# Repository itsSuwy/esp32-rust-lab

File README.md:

# Rust_ESP32_STD
## Descripcion
Este repositorio nacio de la idea de tener un laboratorio personal de proyectos utilizando una placa de desarrollo ESP32, no obstante, a diferencia de repositorios o proyectos utilizando el mismo hardware, aqui se desarrollaran proyectos con el lenguaje de programacion "**Rust**", mas especificamente a su version STD en arquitectura Xtensa respaldada por Espressif. Ya que Rust en sistemas embebidos, microcontroladores y microprocesadores esta ganando fuerza, por lo que me gustaria aprender y dominar este ambito (no me cierro a trabajar con la version no std a futuro!).  
Por otra parte me gustaria que este repositorio pudiera servir de ayuda con los proyectos ya realizados a quienes estan empezando en este ecosistema, ya que encontrar informacion orientada a std, almenos para mi se me complico encontrar.

## Objetivos del repositorio
Ademas de documentar proyectos realizados y poder ayudar a personas nuevas, me gustaria que el destino manifiesto de este proyecto se apegara a los siguientes lineamientos
- Aprender Rust en sistemas **std**.
- Documentar cada proyecto desde cero.
- Presentar ejemplos reproducibles.
- Mantener buenas practicas en el desarrollo.
- Priorizar soluciones técnicamente correctas y eficientes, manteniendo un código claro y mantenible.
- Aspirar a trabajar con proyectos mas "demandantes" segun vaya progresando en los trabajos.

## Contenido
Dentro de este repositorio existiran multiples carpetas asociadas a un proyecto especifico (blinking-leds, comunicacion UART, etc) las cuales contendran toda la informacion que se utilizo para realizarlo. Dentro de cada trabajo la informacion mantendra un orden jerarquizado en dos categorias principales:
- Codigo: Toda la logica para el funcionamiento, incluira un README.md que explique hace cada parte del codigo asi como los componentes que se utilizaron para crearlo con una protoboard. Segun se progrese en la complejidad del trabajo, se comenzaran a omitir ciertos elementos que ya se explicaron en proyectos pasados, para asi evitar saturar el README.md de informacion que ya ha aparecido en otros proyectos, siguiendo un estilo KISS.
- Hardware: Una carpeta exclusiva dentro del directorio del proyecto, contendra: archivo esquematico, diseño de PCB, Project File, los tres siendo nativos de KiCAD. Tambien se adjuntara una o varias fotos del circuito armado en una Protoboard funcionando.

## Cronologia de actividades
Mi meta es pasar de lo basico a lo particular/nicho con este trabajo orientandolo mas a sistemas IoT, por ende decidi separar por etapas los proyectos a realizar, cada una conteniendo varios proyectos y respetando su enfoque comun. Las fases que decidi seguir son:

### Etapa 1: Fundamentos de hardware abstraction
Primera etapa del aprendizaje. Aqui se desarrollaran las bases para el trabajo en sistemas embebidos enfocadas a comprender el funcionamiento del `HAL` (Hardware Abstraction Layer) proporcionado por la libreria oficial de Espressif para abstraer el acceso al ESP-IDF desde Rust. Se aprende a interactual con los perifericos fundamentales del microcontrolador aplicando funciones de: GPIO, UART, PWM, ADC y temporizadores. Estableciendo los conceptos que serviran de base para etapas posteriores.

### Etapa 2: Patrones de Diseño para Sistemas Embebidos
Etapa enfocada en la construcción de aplicaciones embebidas mediante patrones de diseño fundamentales. A partir de los periféricos estudiados anteriormente, se implementan máquinas de estados, integración de múltiples módulos, control de dispositivos de salida y procesamiento básico de datos provenientes de sensores. El objetivo es desarrollar un diseno de codigo modular, escalable y fácil de mantener, siguiendo una arquitectura que pueda reutilizarse en proyectos de mayor complejidad.

### Etapa 3: Comunicación entre Plataformas
Etapa enfocada en el diseño e implementación de arquitecturas distribuidas mediante la comunicación entre múltiples microcontroladores. Se desarrollan protocolos de intercambio de datos, análisis e interpretación de comandos, asignación de responsabilidades entre dispositivos y coordinación del comportamiento del sistema mediante máquinas de estados distribuidas. El objetivo es comprender cómo construir sistemas embebidos compuestos por varios nodos que colaboran entre sí de forma confiable y escalable.

### Etapa 4: Buses de Comunicación
Etapa dedicada al aprendizaje de los principales protocolos de comunicación utilizados en sistemas embebidos para la interacción con periféricos externos. Se implementan interfaces basadas en **I2C** y **SPI**, comprendiendo su funcionamiento, la conexión de múltiples dispositivos sobre un mismo bus y el desarrollo de interfaces gráficas básicas para la visualización de información. El objetivo es adquirir las bases necesarias para integrar sensores, memorias, pantallas y otros periféricos en aplicaciones embebidas de mayor complejidad.

### Etapa 5: Integración de Sensores
Etapa orientada a la adquisición y procesamiento de datos provenientes de sensores utilizados en aplicaciones embebidas reales. Se trabaja con sensores ambientales, de movimiento, de distancia y convertidores analógico-digitales de alta resolución, abordando tanto protocolos de comunicación como requisitos específicos de temporización y precisión. El objetivo es desarrollar la capacidad de integrar múltiples fuentes de información para construir sistemas capaces de percibir e interpretar su entorno.

### Etapa 6: Comunicación Inalámbrica
Etapa dedicada al desarrollo de sistemas embebidos capaces de intercambiar información sin conexión física. Se implementan enlaces mediante transceptores de radiofrecuencia y redes Wi-Fi, abordando el diseño de protocolos de comunicación, el intercambio confiable de datos y la integración con servicios IoT utilizando MQTT. El objetivo es comprender las bases de la conectividad inalámbrica aplicada a sistemas embebidos modernos.

### Etapa 7: Redes LoRa
Etapa enfocada en el desarrollo de sistemas de comunicación de largo alcance y bajo consumo utilizando tecnología LoRa. Se implementan enlaces punto a punto, nodos sensores autónomos y arquitecturas de adquisición de datos con múltiples dispositivos, comprendiendo los principios de las redes de telemetría para aplicaciones distribuidas e IoT.

### Etapa 8: Proyectos Integradores
Etapa destinada a consolidar los conocimientos adquiridos mediante el desarrollo de aplicaciones embebidas completas. Cada proyecto integra múltiples periféricos, protocolos de comunicación, sensores, actuadores y patrones de diseño estudiados en las etapas anteriores, permitiendo aplicar los conceptos en escenarios representativos de sistemas embebidos reales antes de avanzar hacia contenidos de mayor complejidad.

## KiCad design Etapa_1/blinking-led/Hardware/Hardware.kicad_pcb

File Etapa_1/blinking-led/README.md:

## Guía de Funcionamiento

### Descripción
Esta práctica consistió en encender un diodo LED (rojo) utilizando los pines de una placa ESP32-S3 y un transistor BJT NPN 2N2222. Con esto se busca explicar los conceptos básicos del funcionamiento de Rust en arquitecturas de microcontroladores de la familia ESP32.

Los planos de conexiones esquemáticas, el diseño de PCB y una fotografía del circuito en la protoboard se encuentran en la carpeta `Hardware/`.

### Herramientas
- Placa de desarrollo ESP32 (para esta práctica se utilizó el modelo S3-N16R8).
- Un diodo LED (esta práctica utilizó uno de color rojo).
- Un transistor BJT NPN 2N2222.
- Una resistencia de 2.2kΩ.
- Una resistencia de 330Ω.
- Los cables necesarios para las conexiones.

## Código
### Importación de módulos y funciones
Este código opera utilizando `esp_idf_svc`, que es la librería principal de Espressif para proyectos que involucran la versión std de Rust en ESP32. Dentro de este crate (biblioteca) se utiliza el módulo `HAL` (Hardware Abstraction Layer). El funcionamiento de `HAL` es actuar como traductor de funciones complejas del SDK de C nativo de la ESP32 a tipos de datos y estructuras idiomáticas de Rust.
Una vez cargada la capa de abstracción, se cargaron los módulos específicos a utilizar.

**Módulos utilizados:**
- `peripherals` = módulo para gestión global del chip
- `gpio` = módulo para entradas y salidas digitales
- `delay` = módulo para el control de tiempo

Cada módulo incluye su propia función interna para trabajar el propósito por el cual fue incluido:
- `peripherals -> Peripherals`
- `gpio -> PinDriver`
- `delay -> FreeRtos`
```rust
use esp_idf_svc::hal::{peripherals::Peripherals, gpio::PinDriver, delay::FreeRtos};
```
Es la línea encargada de unificar todo lo mencionado.

### Parche del C-SDK
Como se mencionó arriba, al ser un sistema std, depende de una capa de abstracción de las funciones críticas del SDK de C de la ESP. Para "inyectar" este parche se utiliza la línea:
```rust
esp_idf_svc::sys::link_patches();
```
Esta se encarga de indicarle al compilador que incluya y referencie los parches del C-SDK dentro del binario final tras compilar el proyecto. Esto permite evitar reinicios, panics o comportamientos inesperados/impredecibles dentro del microcontrolador.

### Impresión en consola
Pese a ser opcional y no indispensable, se incluyó una función para imprimir en la terminal cuando el LED esté encendido o apagado. Para poder utilizar esta herramienta de logs, se debe llamar de la biblioteca principal de Espressif la función correspondiente que habilita el uso de logs en terminal, la cual es:
```rust
esp_idf_svc::log::EspLogger::initialize_default();
```
Si se utilizan las funciones de log que se presentarán más adelante en esta explicación, pero no se llama esta función, el código no fallará al compilarse, pero los mensajes no aparecerán en la terminal.

### Control de periféricos
Para que el código funcione adecuadamente con la ESP32, se debe contar con el control de todos sus periféricos. Para lograr esto se utiliza la función:
```rust
let peripherals = Peripherals::take().unwrap();
```
La cual crea una variable de nombre `peripherals` y puede recibir dos valores:
- Si todo sale bien, se le da acceso a **todos los elementos** con los que cuenta la ESP32, luciendo así: `Result::Ok(Peripherals)`.
- Si algo sale mal, recibe un `Err` con la informacion del error (`Result::Err(EspError)`). Por lo general algo sale mal cuando otra variable ya tiene control de los periféricos, y para evitar estos errores, se frena aquí el código. Como dato adicional, una vez que el programa recibe un `Err`, este entra en **panic** y se detiene la ejecución entrando en panic.

Del mismo modo, esta función de retorno de valor se divide en dos partes:
- **Asignación**: `Peripherals::take()` recibe o no el control.
- **Control de error**: `.unwrap()`, en caso de que la operación haya fallado y regrese `None`, se detiene el programa para evitar comportamientos inesperados. No es forzoso utilizar esta función; se puede eliminar esta parte y el código seguiría funcionando, siempre y cuando se implemente manualmente una secuencia para el manejo de errores, aunque esto cambiaría la estructura completa de la función en este apartado.

### Asignación de periféricos
Una vez que se tiene control de los periféricos del microcontrolador, queda asignarlos a variables encargadas de operar con ellos. Para eso utilizamos esta línea:
```rust
let mut pin = PinDriver::output(peripherals.pins.gpio5).unwrap();
```
Nótese que la variable forzosamente tiene que ser mutable, ya que los estados que pueda tener el periférico indican cambios en su comportamiento, cambios que una variable inmutable no podría ofrecer sin entrar en panic. Para este ejemplo, la variable que opera el pin se llama `pin`.
Del mismo modo, esta función de retorno de valor también se divide en dos partes:
- Para **controlar un solo** periférico: `PinDriver::output(peripherals.pins.gpio5)`; en este proyecto se utilizó el pin 5. Es importante aclarar que, dependiendo del modelo, varía la cantidad de pines y, con ello, la función que tienen. Algunos pines de microcontroladores ESP32 tienen propósitos únicos, por lo que se recomienda revisarlos antes de asignarlos.
- **Control de error**: `.unwrap()`, mismo escenario que en el apartado anterior; en caso de presentarse un error con la asignación del pin, el programa entra automáticamente en panic para evitar comportamiento indefinido.

### Bucle central
En este apartado se evaluará el flujo que existe dentro del `loop` del código:
- Encender el LED: `pin.set_high().unwrap();`
- Imprimir en la terminal: `log::info!("LED encendido");`. Recuerda que para utilizar esto debiste llamar la función que se encuentra en el apartado **Impresión en consola**.
- Esperar 1 segundo: `FreeRtos::delay_ms(1000);`. Nótese que el tiempo está en milisegundos.
- Apagar el LED: `pin.set_low().unwrap();`

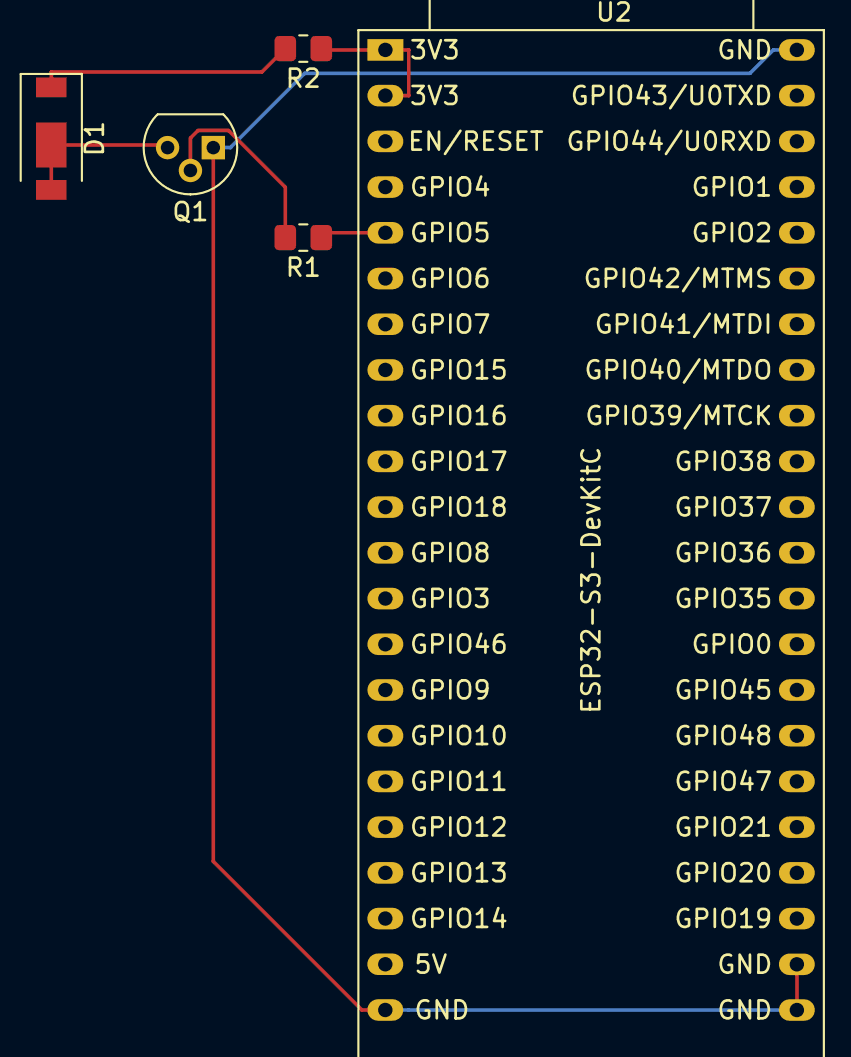
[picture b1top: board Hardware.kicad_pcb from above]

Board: 2 copper layers, 5 parts (0 on the bottom side), 6 nets.

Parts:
D1: LED; LED_Yuji_5730
Q1: PN2222A; TO-92
R1: 2k2; R_0805_2012Metric_Pad1.20x1.40mm_HandSolder
R2: 330; R_0805_2012Metric_Pad1.20x1.40mm_HandSolder
U2: ESP32-S3-DevKitC

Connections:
/3v3: R2.1, U2.1 (3V3), U2.2 (3V3)
/GND: Q1.1 (E), U2.22 (GND), U2.23 (GND), U2.24 (GND), U2.44 (GND)
unnamed: D1.2 (A), Q1.3 (C)
unnamed: D1.1 (K), R2.2
unnamed: Q1.2 (B), R1.2
unnamed: R1.1, U2.5 (GPIO5/ADC1_CH4)
